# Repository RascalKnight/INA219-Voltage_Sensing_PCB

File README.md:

# INA219 Current/Power Monitor Board

A 4-layer PCB for high-side current and power sensing using the TI 
INA219, built as a self-directed mixed-signal design exercise. This 
board bridges an analog current-sense front end with a digital I2C 
interface, and was the first project in this series to require real 
attention to signal isolation and layer planning rather than single-layer 
routing.

## Overview

The board measures current through a 4-terminal Kelvin-sense shunt 
resistor placed in the high-side power path (POWER in → shunt → LOAD 
out), and reports current, bus voltage, and power over I2C via the 
INA219. It's designed as an in-line sensor: the board only carries the 
positive/hot side of the current path, with the circuit's return path 
completed externally through the system's own ground wiring.

## Key Design Features

- **INA219AxDCN** current/power monitor IC
- **4-terminal Kelvin-sense shunt resistor** (10mΩ), with dedicated sense 
  taps landing directly on the shunt's own sense pads — not tapped 
  further down the power trace — to avoid measurement error from trace 
  resistance
- **RC filter network** (10Ω + 0.1µF) on the IN+/IN- sense lines per 
  TI's recommended application circuit, to reduce noise reaching the 
  PGA's sensitive input stage
- **4-layer stackup** with a dedicated internal ground plane, chosen 
  specifically to give the analog sense signals and digital I2C lines a 
  clean, consistent return path without them competing for the same 
  copper
- Standard I2C pull-ups (3.3kΩ) and VS decoupling (0.1µF)

## Design Challenges Solved

- **Signal separation to avoid crosstalk**: worked through how to 
  physically separate the analog sense path (shunt → filter → INA219 
  input) from the digital I2C lines, so switching noise on SDA/SCL 
  doesn't couple into the sensitive current measurement
- **Junction planning to minimize vias on the ground plane**: rather than 
  routing every ground connection down through a via, used junctions and 
  layer choice deliberately to keep the internal ground plane as 
  continuous as possible, avoiding unnecessary Swiss-cheesing of the 
  reference plane
- **Kelvin sensing implementation**: correctly separated the 
  high-current power path pins from the low-current sense pins on the 
  shunt resistor, both in schematic and layout, to get an accurate 
  measurement

## Files

- `.kicad_sch` / `.kicad_pcb` — full KiCad source project
- Schematic PDF export
- 3D board render

## Tools

Designed entirely in KiCad 10.

## Status

Schematic and PCB complete.

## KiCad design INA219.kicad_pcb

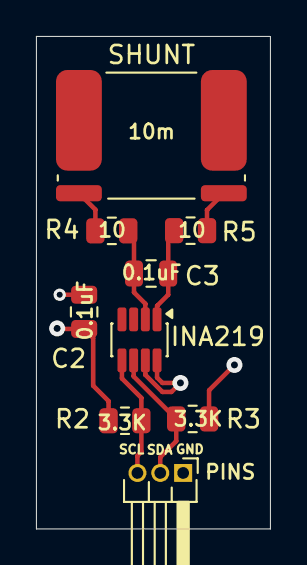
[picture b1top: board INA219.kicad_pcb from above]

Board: 4 copper layers, 13.0 x 27.4 mm, 9 parts (0 on the bottom side), 8 nets.

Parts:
C2, C3: 0.1uF; C_0805_2012Metric
INA219: INA219AxDCN; SOT-23-8
PINS: Conn_01x03_Pin; PinHeader_1x03_P1.27mm_Horizontal
R2, R3: 3.3K; R_0805_2012Metric
R4, R5: 10; R_0805_2012Metric
SHUNT: 10m; R_Shunt_Isabellenhuette_BVR4026

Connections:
+5V: C2.2, INA219.4 (VS), R2.1, R3.1
/IN+: C3.2, INA219.1 (IN+), R5.2
/IN-: C3.1, INA219.2 (IN-), R4.2
/SCL: INA219.5 (SCL), PINS.3, R2.2
/SDA: INA219.6 (SDA), PINS.2, R3.2
GND: C2.1, INA219.3 (GND), INA219.7 (A0), INA219.8 (A1), PINS.1
unnamed: R4.1, SHUNT.2
unnamed: R5.1, SHUNT.3
